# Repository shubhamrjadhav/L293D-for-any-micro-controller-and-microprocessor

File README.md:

# L293D-for-any-micro-controller-and-microprocessor
It is eagle design for an dc motor driver ic l293d which can be interfaced with and controller and processor

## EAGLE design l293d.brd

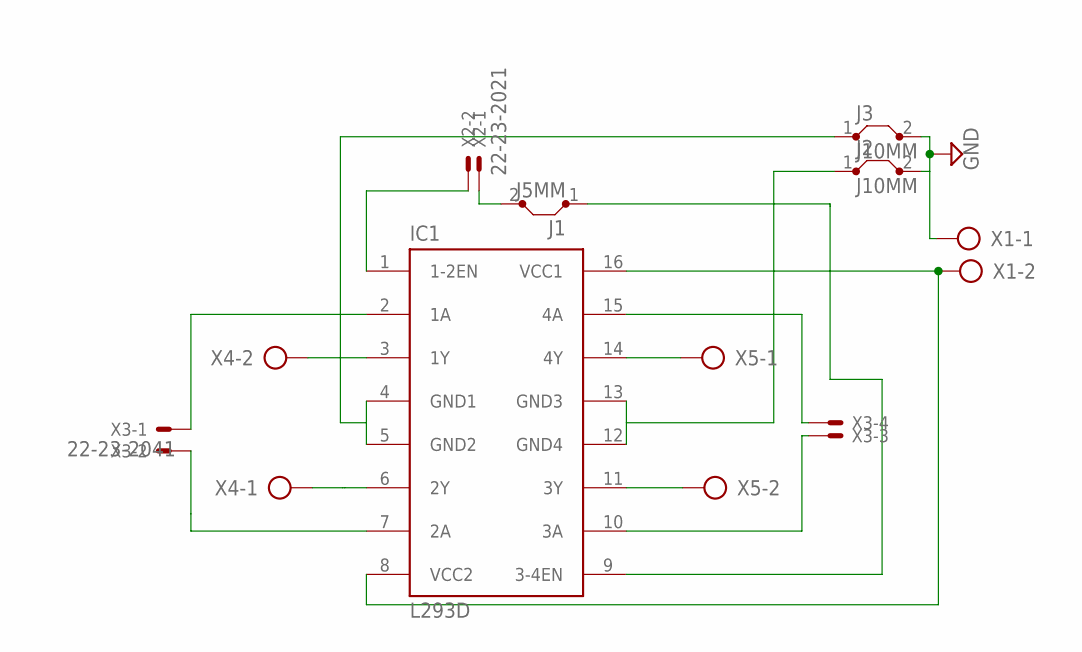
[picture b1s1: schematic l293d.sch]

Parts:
IC1: L293D; DIL16
J1: J5MM; 05
J2, J3: J10MM; 10
X1, X4, X5: AK500/2
X2: 22-23-2021
X3: 22-23-2041

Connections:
GND: J2.2, J3.2, X1.1
unnamed: IC1.10 (3A), X3.3
unnamed: IC1.8 (VCC2), IC1.16 (VCC1), X1.2
unnamed: IC1.2 (1A), X3.1
unnamed: IC1.14 (4Y), X5.1
unnamed: IC1.12 (GND4), IC1.13 (GND3), J2.1
unnamed: IC1.15 (4A), X3.4
unnamed: IC1.1 (1-2EN), X2.2
unnamed: IC1.9 (3-4EN), J1.1
unnamed: IC1.3 (1Y), X4.2
unnamed: IC1.6 (2Y), X4.1
unnamed: IC1.11 (3Y), X5.2
unnamed: IC1.4 (GND1), IC1.5 (GND2), J3.1
unnamed: J1.2, X2.1
unnamed: IC1.7 (2A), X3.2

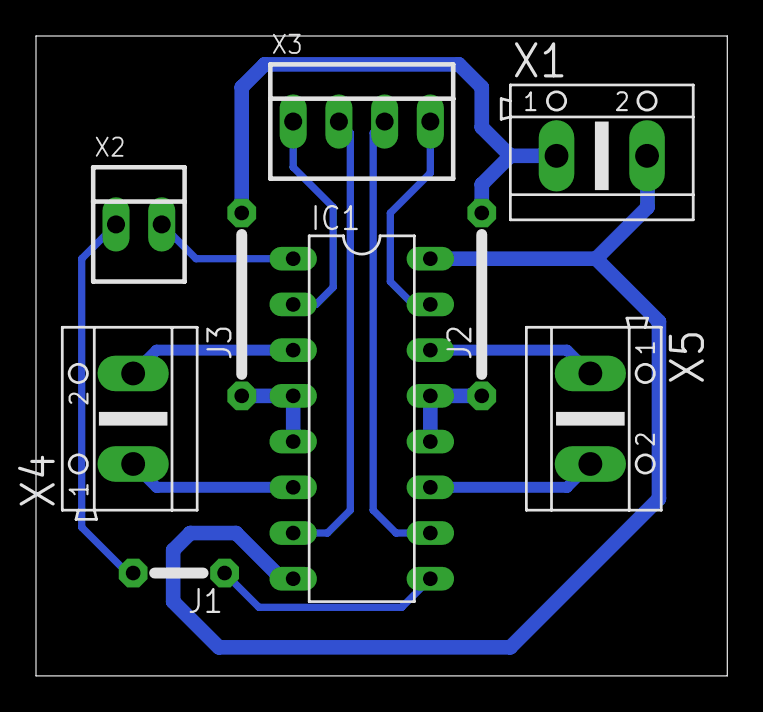
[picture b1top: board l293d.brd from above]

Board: 2 copper layers, 38.4 x 35.5 mm, 9 parts (0 on the bottom side), 15 nets.
